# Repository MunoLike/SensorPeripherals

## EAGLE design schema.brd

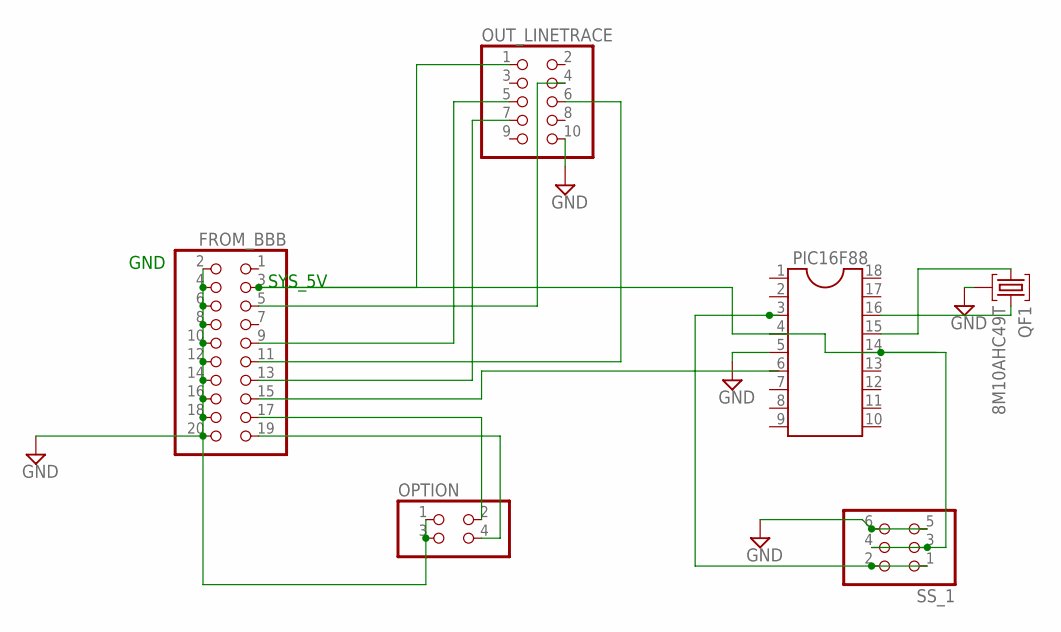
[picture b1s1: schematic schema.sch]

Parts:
FROM_BBB: PINHD-2X10; 2X10
OPTION: PINHD-2X2; 2X02
OUT_LINETRACE: PINHD-2X5; 2X05
PIC16F88: DIL18S; SOCKET-18
QF1: 8M10AHC49T; HC49U
SS_1: PINHD-2X3; 2X03

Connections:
GND: FROM_BBB.2, FROM_BBB.4, FROM_BBB.6, FROM_BBB.8, FROM_BBB.10, FROM_BBB.12, FROM_BBB.14, FROM_BBB.16, FROM_BBB.18, FROM_BBB.20, OPTION.1, OPTION.3, OUT_LINETRACE.10, PIC16F88.5, QF1.2, SS_1.5, SS_1.6
unnamed: FROM_BBB.5, OUT_LINETRACE.4
unnamed: FROM_BBB.9, OUT_LINETRACE.5
unnamed: FROM_BBB.11, OUT_LINETRACE.6
unnamed: FROM_BBB.13, OUT_LINETRACE.7
unnamed: PIC16F88.3, SS_1.1, SS_1.2
unnamed: FROM_BBB.3, OUT_LINETRACE.1, PIC16F88.4, PIC16F88.14, SS_1.3, SS_1.4
unnamed: PIC16F88.15, QF1.1
unnamed: PIC16F88.16, QF1.3
unnamed: FROM_BBB.17, OPTION.2
unnamed: FROM_BBB.19, OPTION.4

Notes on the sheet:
SYS_5V
GND

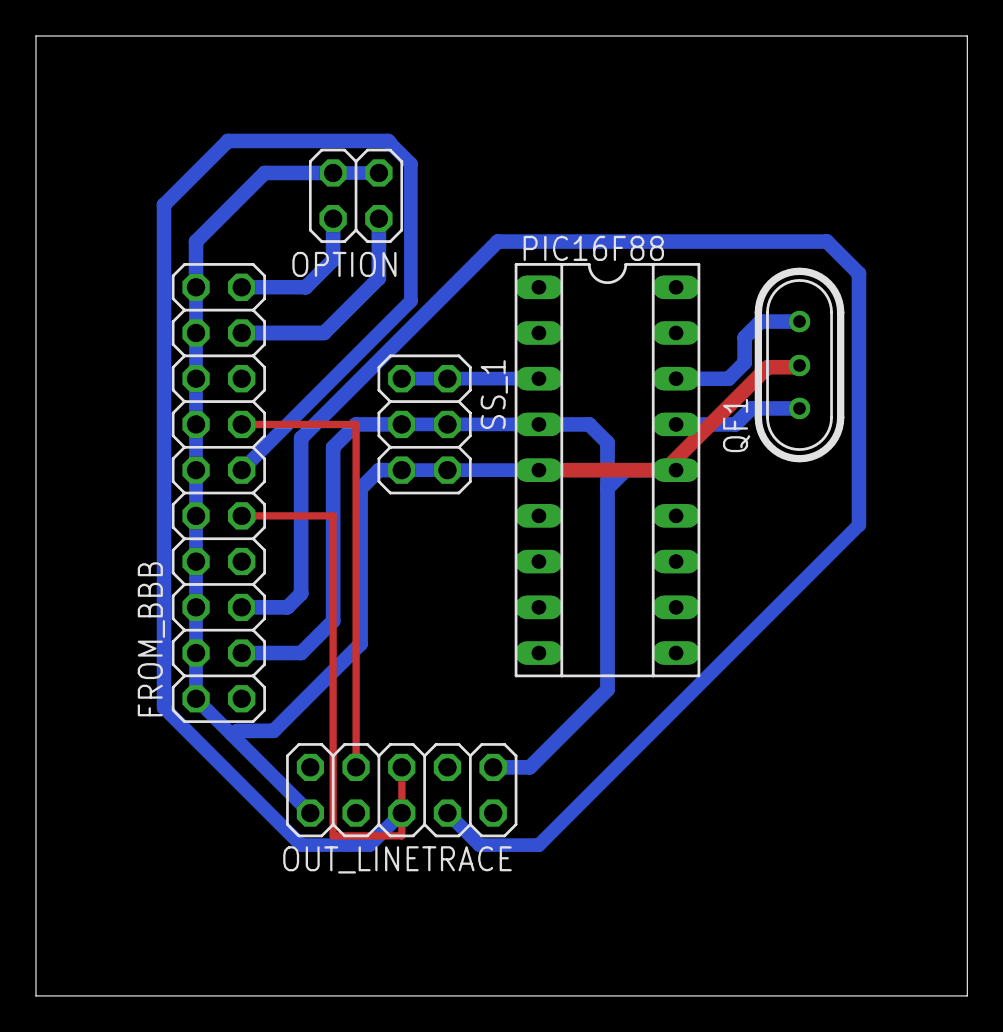
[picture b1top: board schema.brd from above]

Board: 2 copper layers, 51.7 x 53.3 mm, 6 parts (0 on the bottom side), 11 nets.

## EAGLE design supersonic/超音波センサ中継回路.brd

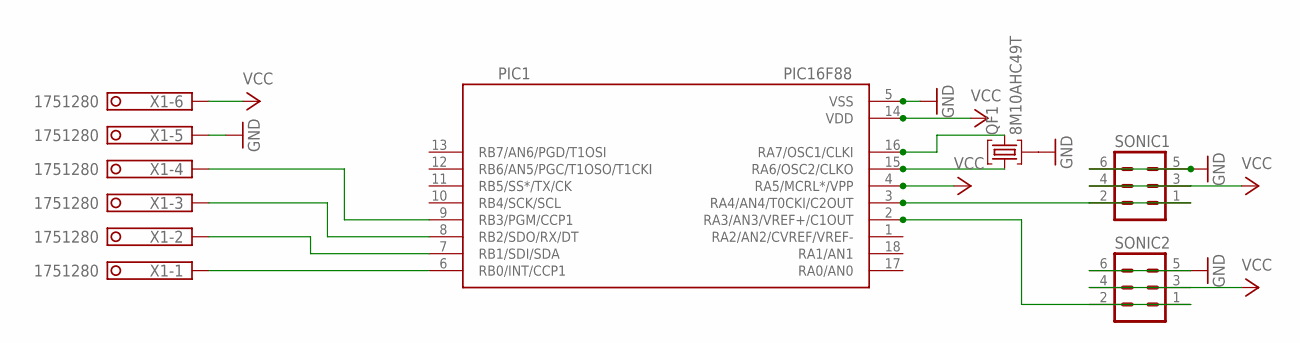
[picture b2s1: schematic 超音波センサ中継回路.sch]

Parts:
PIC1: PIC16F88; DIL18
QF1: 8M10AHC49T; HC49U
SONIC1, SONIC2: ML6
X1: 1751280

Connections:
GND: PIC1.5 (VSS), QF1.2, SONIC1.5, SONIC1.6, SONIC2.5, SONIC2.6, X1.5
unnamed: PIC1.9 (RB3/PGM/CCP1), X1.4
unnamed: PIC1.6 (RB0/INT/CCP1), X1.1
unnamed: PIC1.2 (RA3/AN3/VREF+/C1OUT), SONIC2.1, SONIC2.2
unnamed: PIC1.7 (RB1/SDI/SDA), X1.2
unnamed: PIC1.3 (RA4/AN4/T0CKI/C2OUT), SONIC1.1, SONIC1.2
unnamed: PIC1.8 (RB2/SDO/RX/DT), X1.3
unnamed: PIC1.15 (RA6/OSC2/CLKO), QF1.1
unnamed: PIC1.16 (RA7/OSC1/CLKI), QF1.3
VCC: PIC1.4 (RA5/MCRL*/VPP), PIC1.14 (VDD), SONIC1.3, SONIC1.4, SONIC2.3, SONIC2.4, X1.6

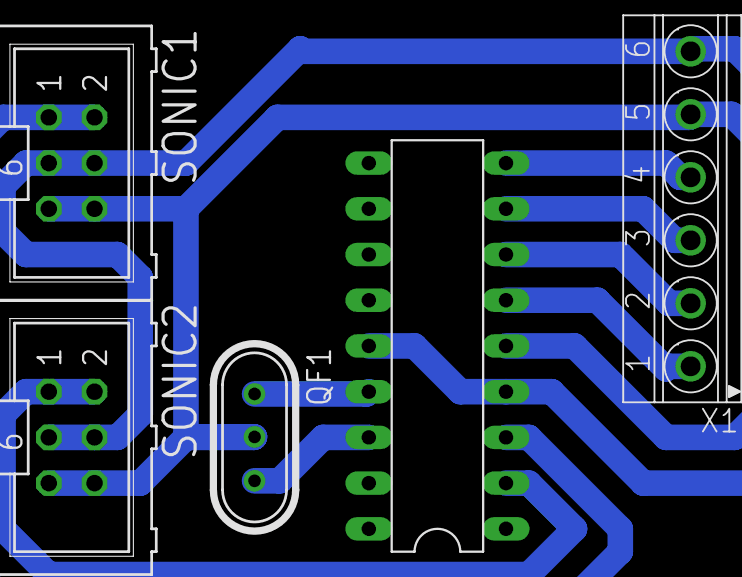
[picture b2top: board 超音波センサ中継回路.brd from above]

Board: 2 copper layers, 5 parts (0 on the bottom side), 10 nets.

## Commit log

2020-11-14 trimmed the corners
2020-11-14 add PDFs and correct wrong wiring from Crystal Generator to SYS_5V
